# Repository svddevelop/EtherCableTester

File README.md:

# EtherCableTester
The little electronics project, based on CH32V003F8P6 for the test of the ethernet cable.

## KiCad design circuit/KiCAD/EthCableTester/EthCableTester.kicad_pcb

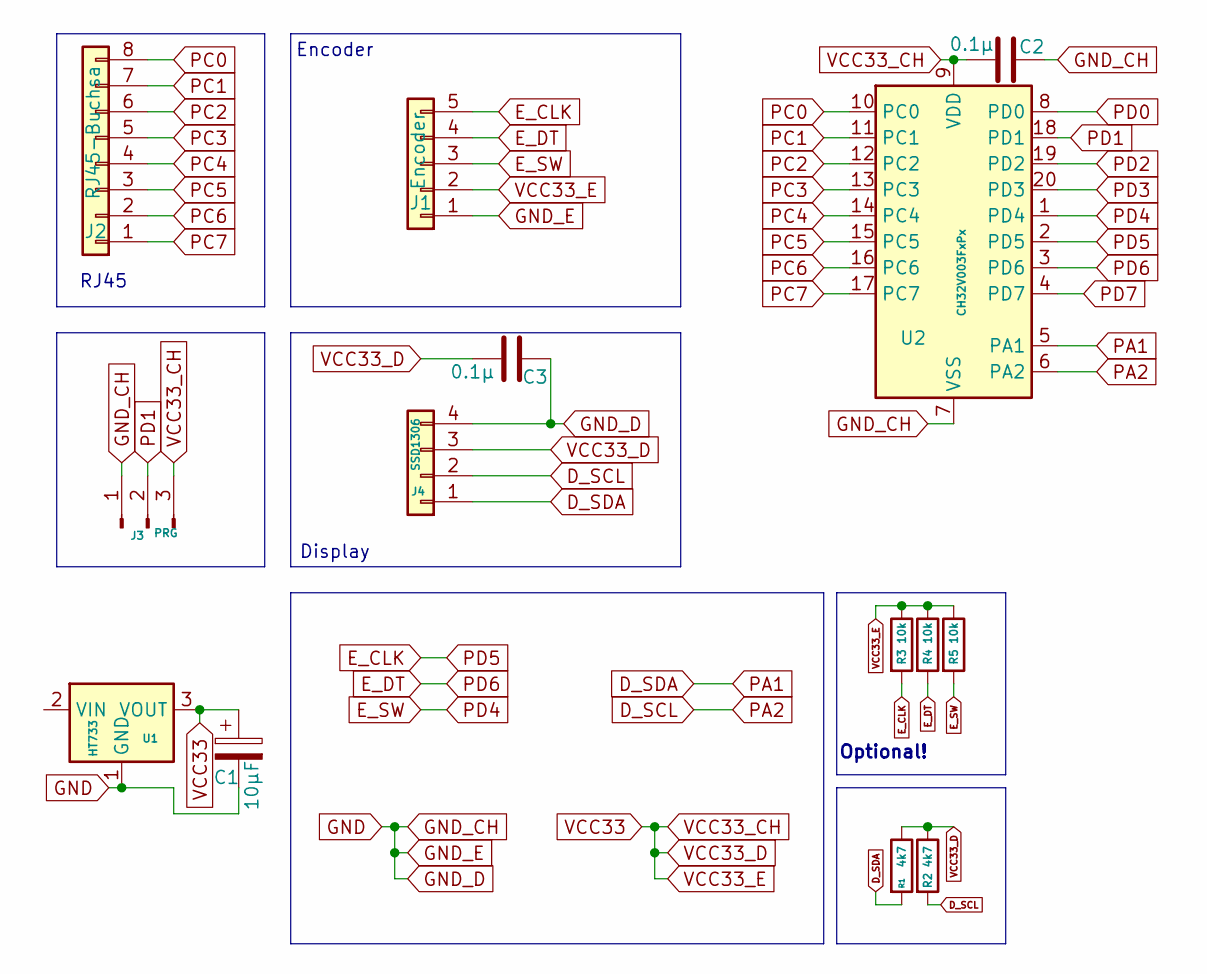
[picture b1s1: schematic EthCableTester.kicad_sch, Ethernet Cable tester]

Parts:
C1: 10µF; CP_Elec_8x10
C2, C3: 0.1µ; C_0805_2012Metric
J1: Encoder; PinHeader_1x05_P2.54mm_Horizontal
J2: RJ45-Buchsa; PinSocket_1x08_P2.54mm_Vertical
J3: PRG; PinHeader_1x03_P2.54mm_Vertical
J4: SSD1306; PinHeader_1x04_P2.54mm_Horizontal
R1, R2: 4k7; R_0805_2012Metric
R3, R4, R5: 10k; R_0805_2012Metric
U1: HT733; TO-252-3_TabPin2
U2: CH32V003FxPx; TSSOP-20_4.4x6.5mm_P0.65mm

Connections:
D_SCL: J4.2, R2.2, U2.6 (PA2)
D_SDA: J4.1, R1.2, U2.5 (PA1)
E_CLK: J1.5, R3.2, U2.2 (PD5)
E_DT: J1.4, R4.2, U2.3 (PD6)
E_SW: J1.3, R5.2, U2.1 (PD4)
GND: C1.2, C2.2, C3.2, J1.1, J3.1, J4.4, U1.1 (GND), U2.7 (VSS)
PC0: J2.8, U2.10 (PC0)
PC1: J2.7, U2.11 (PC1)
PC2: J2.6, U2.12 (PC2)
PC3: J2.5, U2.13 (PC3)
PC4: J2.4, U2.14 (PC4)
PC5: J2.3, U2.15 (PC5)
PC6: J2.2, U2.16 (PC6)
PC7: J2.1, U2.17 (PC7)
PD0: U2.8 (PD0)
PD1: J3.2, U2.18 (PD1)
PD2: U2.19 (PD2)
PD3: U2.20 (PD3)
PD7: U2.4 (PD7)
VCC33: C1.1, C2.1, C3.1, J1.2, J3.3, J4.3, R1.1, R2.1, R3.1, R4.1, R5.1, U1.3 (VOUT), U2.9 (VDD)

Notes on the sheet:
Display
Optional!
RJ45
Encoder

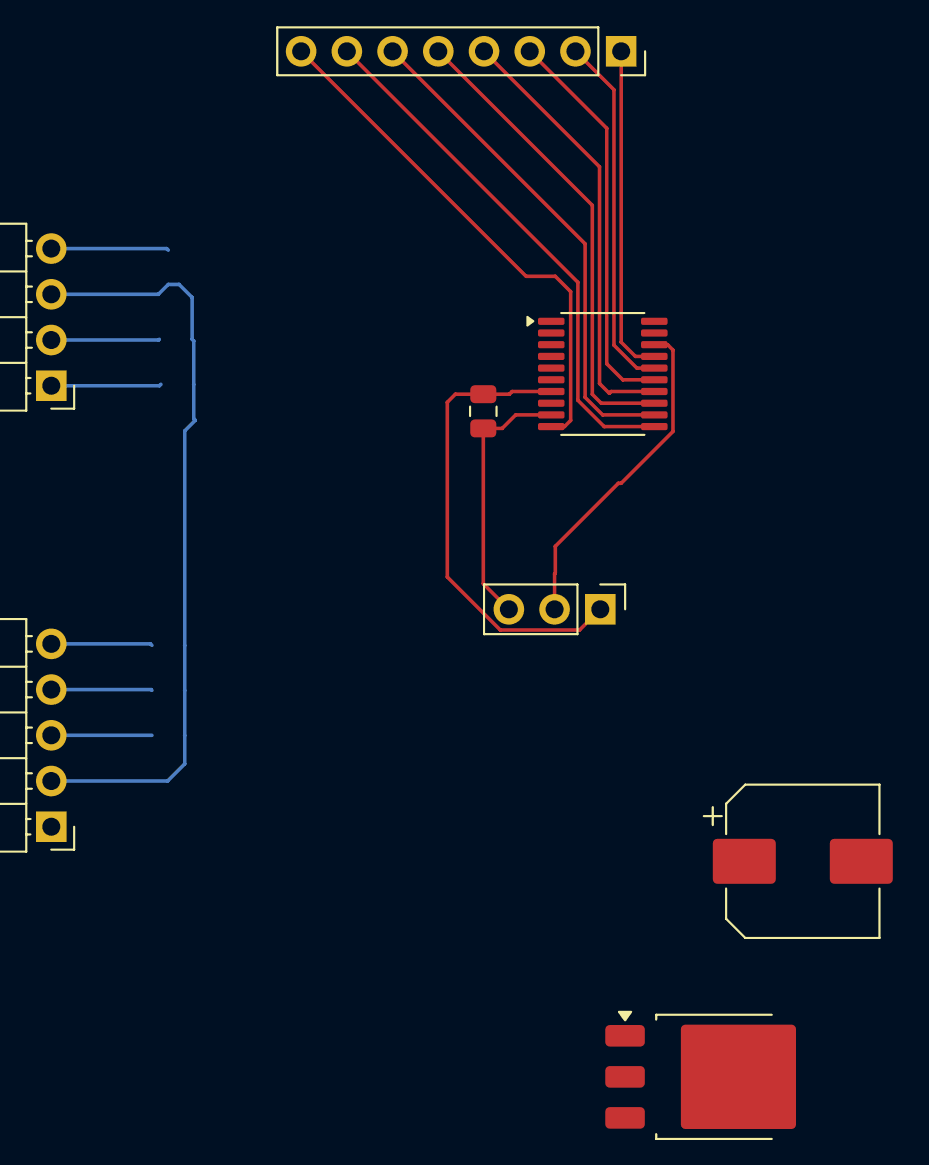
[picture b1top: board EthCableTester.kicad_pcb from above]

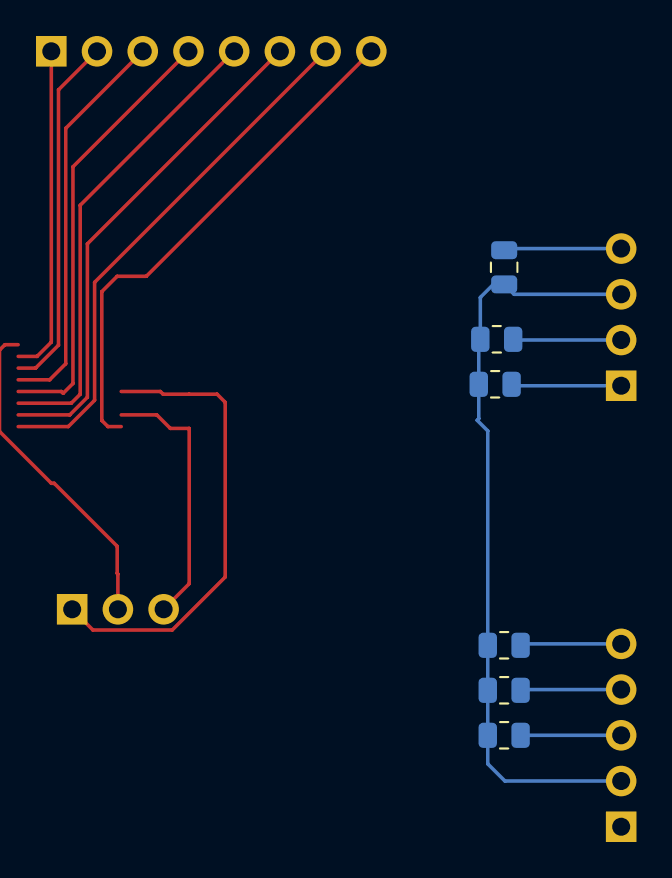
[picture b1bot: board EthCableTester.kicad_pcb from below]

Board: 2 copper layers, 14 parts (6 on the bottom side), 16 nets.

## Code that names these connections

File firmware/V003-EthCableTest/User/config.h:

// ===================================================================================
// Project:   Ethernet Cable Tester - Pin and System Configuration
// Chip:      CH32V003A4M6 (SOP-16)
// ===================================================================================
//
// Pin allocation (14 GPIO available, SWIO/PD1 reserved for programming only):
//
//   RJ45 contact 1 -> PC0   |  Encoder A   -> PD5   (EXTI line 5)
//   RJ45 contact 2 -> PC1   |  Encoder B   -> PD6   (EXTI line 6, input only)
//   RJ45 contact 3 -> PC2   |  Encoder SW  -> PD7   (EXTI line 7)
//   RJ45 contact 4 -> PC3   |
//   RJ45 contact 5 -> PC4   |  I2C SDA     -> PA1   (soft I2C, SSD1306)
//   RJ45 contact 6 -> PC6   |  I2C SCL     -> PA2   (soft I2C, SSD1306)
//   RJ45 contact 7 -> PC7   |
//   RJ45 contact 8 -> PD4   |  SWIO (PD1)  -> WCH-LinkE programmer ONLY
//
// Notes:
// - All three encoder inputs use EXTI lines with different pin numbers
//   (5, 6, 7), which is required by the single EXTI port multiplexer.
// - PC0..PC4, PC6, PD4 occupy physically adjacent package pins (16,1,2,3,4,5,8),
//   which keeps the RJ45 wiring short and uniform. PD1 (pin 7) sits between
//   PC7 and PD4 but is not routed to the RJ45 socket.
// - PD0/PD2/PD3 are not bonded out on the SOP-16 package, PC5 does not exist
//   on this chip variant.
//
// ===================================================================================
#pragma once

#include "gpio.h"

// --- RJ45 contacts 1..8 -----------------------------------------------------------
#define PIN_RJ1     PC0
#define PIN_RJ2     PC1
#define PIN_RJ3     PC2
#define PIN_RJ4     PC3
#define PIN_RJ5     PC4
//#define PIN_RJ6     PC6
#define PIN_RJ6     PC5
//#define PIN_RJ7     PC7
#define PIN_RJ7     PC6
//#define PIN_RJ8     PD4
#define PIN_RJ8     PC7


//#define RJ45_PINS   { PC0, PC1, PC2, PC3, PC4, PC6, PC7, PD4 }
#define RJ45_PINS   { PC0, PC1, PC2, PC3, PC4, PC5, PC6, PC7 }
#define RJ45_COUNT  8

// --- Rotary encoder with center button --------------------------------------------
#define PIN_ENC_A   PD5                 // EXTI line 5, quadrature input A
#define PIN_ENC_B   PD6                 // EXTI line 6 is free; B is read as plain input
#define PIN_ENC_BTN PD4                 // EXTI line 7, push button (active low)

#define ENC_DEBOUNCE_MS    20           // button debounce time [ms]
#define ENC_LONGPRESS_MS  700           // long press threshold [ms]

// --- SSD1306 128x64 OLED over soft I2C --------------------------------------------
#define PIN_I2C_SDA  PA1
#define PIN_I2C_SCL  PA2
#define OLED_ADDR    0x3C               // 7-bit I2C address of SSD1306 (0x78 write)
#define I2C_DELAY_US   3                // half SCL period -> about 100..150 kHz

// --- Software PWM (used for the '~' pin mode) --------------------------------------
#define PWM_FREQ_HZ   1000              // carrier frequency [Hz]
#define PWM_STEPS     50                // duty resolution (2% per step)

// --- Flash storage ------------------------------------------------------------------
// CH32V003 main flash is 16 KB, organized as 64-byte pages. The controller
// programs and erases them in the 0x08000000 alias (same array as 0x00000000).
#define FLASH_PAGE_SIZE   64
#define FLASH_BASE_ADDR   0x08000000UL
#define FLASH_SIZE        (16 * 1024)
#define FLASH_LAST_PAGE   (FLASH_BASE_ADDR + FLASH_SIZE - FLASH_PAGE_SIZE)

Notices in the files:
circuit/KiCAD/EthCableTester/EthCableTester.kicad_sch:
©SVDDevelop
